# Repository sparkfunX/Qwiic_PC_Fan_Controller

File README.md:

Qwiic PC Fan Controller
========================================

[*Qwiic PC Fan Controller (SPX-18570)*](https://www.sparkfun.com/products/18570)

Whether for active cooling or ventilation, a tiny fan can make a big difference. And by that logic a big fan can make an even bigger difference! Luckily, 4-Wire PC cooling fans come in all shapes and sizes, so there's definitely one out there that's perfect for your project. The only downside is that they can be a pain to drive if you don't need them to be 100% on the throttle all the time. To remedy this, we've modified our Qwiic Blower Fan board to drive any 3- or 4-wire PC Fan with any voltage from 5 to 20VDC!

The Qwiic PC Fan Controller allows you easily control almost any PC fan over the Qwiic bus using the on board ATtiny microcontroller and control firmware. The control firmware monitors the tachometer output of the fan in order to implement PI Control over the fan speed, allowing you to set your desired speed in real units. It's also possible to disable the PI control loop and set the speed as a proportion of the maximum. The accompanying Arduino library includes example code for controlling the fan, tweaking settings, and even setting the fan speed based on an attached Qwiic Temperature Sensor and a lookup table. The on board trimpots allow you to very quickly tune the PI loop parameters to your application, but they can also be overridden by the Qwiic bus for remote configuration.

Heads Up! Without any external power supply connected, the Qwiic PC Fan Controller will attempt to drive the connected fan from the Qwiic bus. Even a very small 5V fan operates at the upper limit of the Qwiic bus' power delivery capability. If there are few other devices on the bus and the fan is not allowed to rapidly change throttle, it is possible to power a small fan directly from the bus. In most applications, however, it will be necessary to provide the PC Fan Controller with a dedicated fan power supply.

Repository Contents
-------------------

* **/Firmware** - Control firmware for the ATtiny
* **/Hardware** - Eagle design files (.brd, .sch)
* **/Production** - Panelized hardware files for production

License Information
-------------------

This product is _**open source**_! 

Please review the LICENSE.md file for license information. 

If you have any questions or concerns on licensing, please contact technical support on our [SparkFun forums](https://forum.sparkfun.com/viewforum.php?f=152).

Distributed as-is; no warranty is given.

- Your friends at SparkFun.

_<COLLABORATION CREDIT>_

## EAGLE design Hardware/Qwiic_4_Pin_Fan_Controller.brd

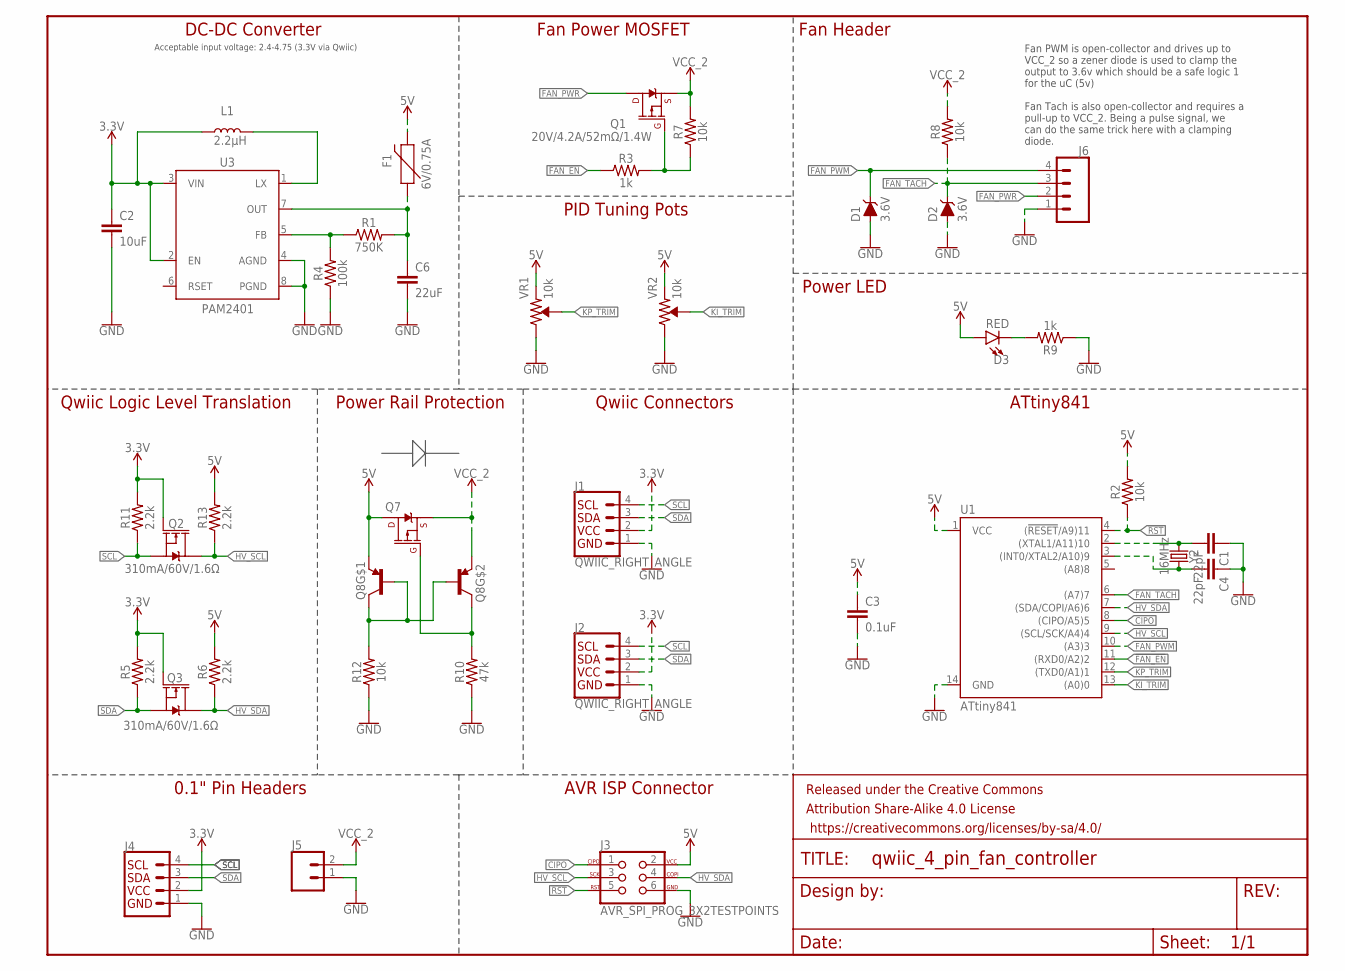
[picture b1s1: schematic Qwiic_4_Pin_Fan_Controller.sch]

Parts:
C1, C4: 22pF; 0603
C2: 10uF; 0603
C3: 0.1uF; 0603
C6: 22uF; 0805
D1, D2: 3.6V; SOD-323
D3: RED; LED-0603
F1: 6V/0.75A; 1206
FRAME1: FRAME-LETTER; CREATIVE_COMMONS
J1, J2: QWIIC_RIGHT_ANGLE; JST04_1MM_RA
J3: AVR_SPI_PROG_3X2TESTPOINTS; 2X3_TEST_POINTS
J4: I2C_STANDARD_NO_SILK; 1X04_NO_SILK
J5: CONN_021X02_NO_SILK; 1X02_NO_SILK
J6: CONN_041X04_NO_SILK; 1X04_NO_SILK
L1: 2.2μH; 0806
Q1, Q7: 20V/4.2A/52mΩ/1.4W; SOT23-3
Q2, Q3: 310mA/60V/1.6Ω; SOT323
Q8: TRANS_PNP_DUALSOT-363; SOT363_PHILIPS
R1: 750K; 0603
R2, R7, R8, R12: 10k; 0603@1
R3, R9: 1k; 0603
R4: 100k; 0603
R5, R6, R11, R13: 2.2k; 0603
R10: 47k; 0603@1
U1: ATtiny841; SO14
U3: PAM2401; MSOP8
VR1, VR2: 10k; TRIMPOT-SMD-3MM-CLOSED
Y2: 16MHz; CRYSTAL-SMD-2.0X1.6MM

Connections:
3.3V: C2.1, J1.2, J2.2, J4.2, L1.1, Q2.1 (G), Q3.1 (G), R5.2, R11.2, U3.2 (EN), U3.3 (VIN)
5V: C3.1, D3.A, F1.2, J3.2, Q7.3 (D), Q8.1 (E), R2.2, R6.2, R13.2, U1.1 (VCC), VR1.1 (CCW), VR2.1 (CCW)
!FAN_EN: R3.1, U1.11 ((RXD0/A2)2)
!RST: J3.5, R2.1, U1.4 ((!RESET!/A9)11)
CIPO: J3.1, U1.8 ((CIPO/A5)5)
FAN_PWM: D1.C, J6.4, U1.10 ((A3)3)
FAN_PWR: J6.2, Q1.3 (D)
FAN_TACH: D2.C, J6.3, R8.1, U1.6 ((A7)7)
GND: C1.1, C2.2, C3.2, C4.1, C6.2, D1.A, D2.A, J1.1, J2.1, J3.6, J4.1, J5.1, J6.1, R4.1, R9.1, R10.1, R12.1, U1.14 (GND), U3.4 (AGND), U3.8 (PGND), VR1.3 (CW), VR2.3 (CW)
HV_SCL: J3.3, Q2.3 (D), R13.1, U1.9 ((SCL/SCK/A4)4)
HV_SDA: J3.4, Q3.3 (D), R6.1, U1.7 ((SDA/COPI/A6)6)
KI_TRIM: U1.13 ((A0)0), VR2.2 (WIPER)
KP_TRIM: U1.12 ((TXD0/A1)1), VR1.2 (WIPER)
unnamed: C4.2, U1.3 ((INT0/XTAL2/A10)9), Y2.1
unnamed: R1.1, R4.2, U3.5 (FB)
unnamed: L1.2, U3.1 (LX)
unnamed: C1.2, U1.2 ((XTAL1/A11)10), Y2.3 (2)
unnamed: Q1.1 (G), R3.2, R7.1
unnamed: C6.1, F1.1, R1.2, U3.7 (OUT)
unnamed: D3.C, R9.2
unnamed: Q7.1 (G), Q8.3 (C), R10.2
unnamed: Q8.2 (B), Q8.5 (B), Q8.6 (C), R12.2
SCL: J1.4, J2.4, J4.4, Q2.2 (S), R11.1
SDA: J1.3, J2.3, J4.3, Q3.2 (S), R5.1
VCC_2: J5.2, Q1.2 (S), Q7.2 (S), Q8.4 (E), R7.2, R8.2

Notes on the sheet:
DC-DC Converter
Acceptable input voltage: 2.4-4.75 (3.3V via Qwiic)
ATtiny841
Qwiic Connectors
Qwiic Logic Level Translation
0.1" Pin Headers
AVR ISP Connector
Fan Power MOSFET
Fan Header
Fan PWM is open-collector and drives up to VCC_2 so a zener diode is used to clamp the output to 3.6v which should be a safe logic 1 for the uC (5v) Fan Tach is also open-collector and requires a pull-up to VCC_2. Being a pulse signal, we can do the same trick here with a clamping diode.
PID Tuning Pots
Power LED
Power Rail Protection

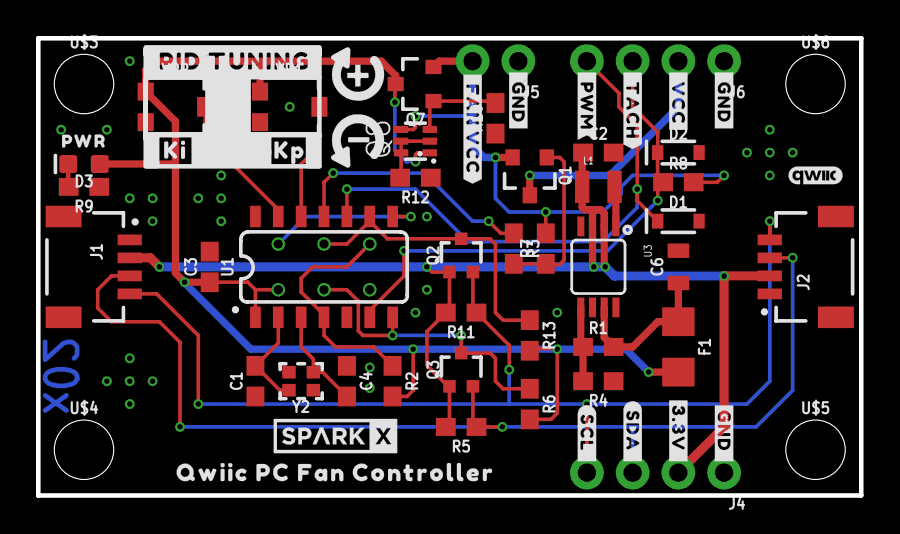
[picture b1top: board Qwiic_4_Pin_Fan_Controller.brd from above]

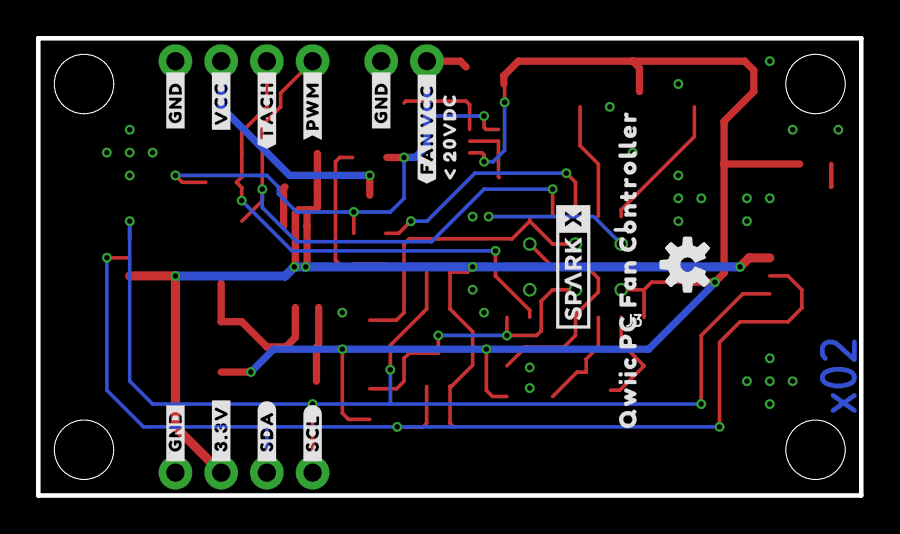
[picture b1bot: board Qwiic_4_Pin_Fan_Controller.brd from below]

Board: 2 copper layers, 45.7 x 25.4 mm, 76 parts (15 on the bottom side), 25 nets.

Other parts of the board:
U$1, U$9, U$21: #_GND#0
U$2: #_VCC#0
U$3, U$4, U$5, U$6: STAND-OFF
U$7: #_TACH#0
U$8: #_PWM#0
U$10, U$20, U$26: #GND_#0
U$11: #3#3V_#0
U$12: #SDA_#0
U$13: #SCL_#0
U$14: #PID_TUNING0
U$15: KI0
U$16: KP0
U$17: QWIIC_3MM
U$18, U$36: SPARKX-SMALL
U$19: #_FAN_VCC#0
U$22: PWR0
U$23: #VCC_#0
U$24: #TACH_#0
U$25: #PWM_#0
U$27: #_3#3V#0
U$28: #_SDA#0
U$29: #_SCL#0
U$30, U$35: QWIIC_PC_FAN_CONTROLLER0
U$31: #FAN_VCC_#0
U$32: _#_20VDC0
U$37: OSHW-LOGO-S
U$38: TURN_INDICATOR#SVG0

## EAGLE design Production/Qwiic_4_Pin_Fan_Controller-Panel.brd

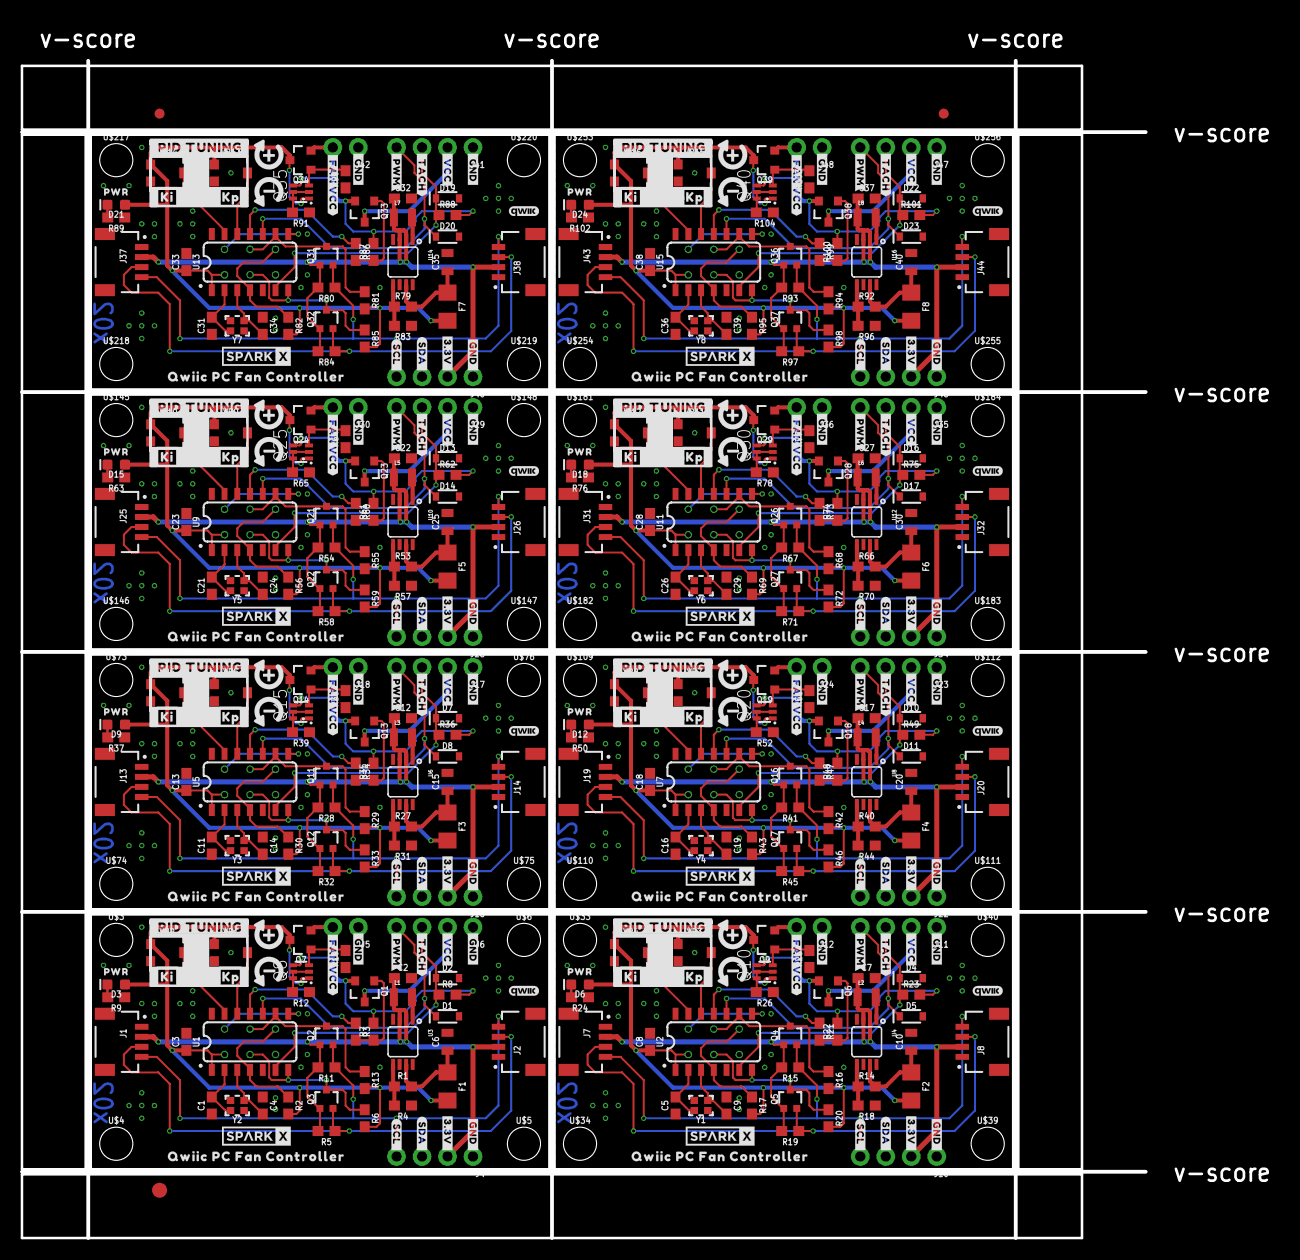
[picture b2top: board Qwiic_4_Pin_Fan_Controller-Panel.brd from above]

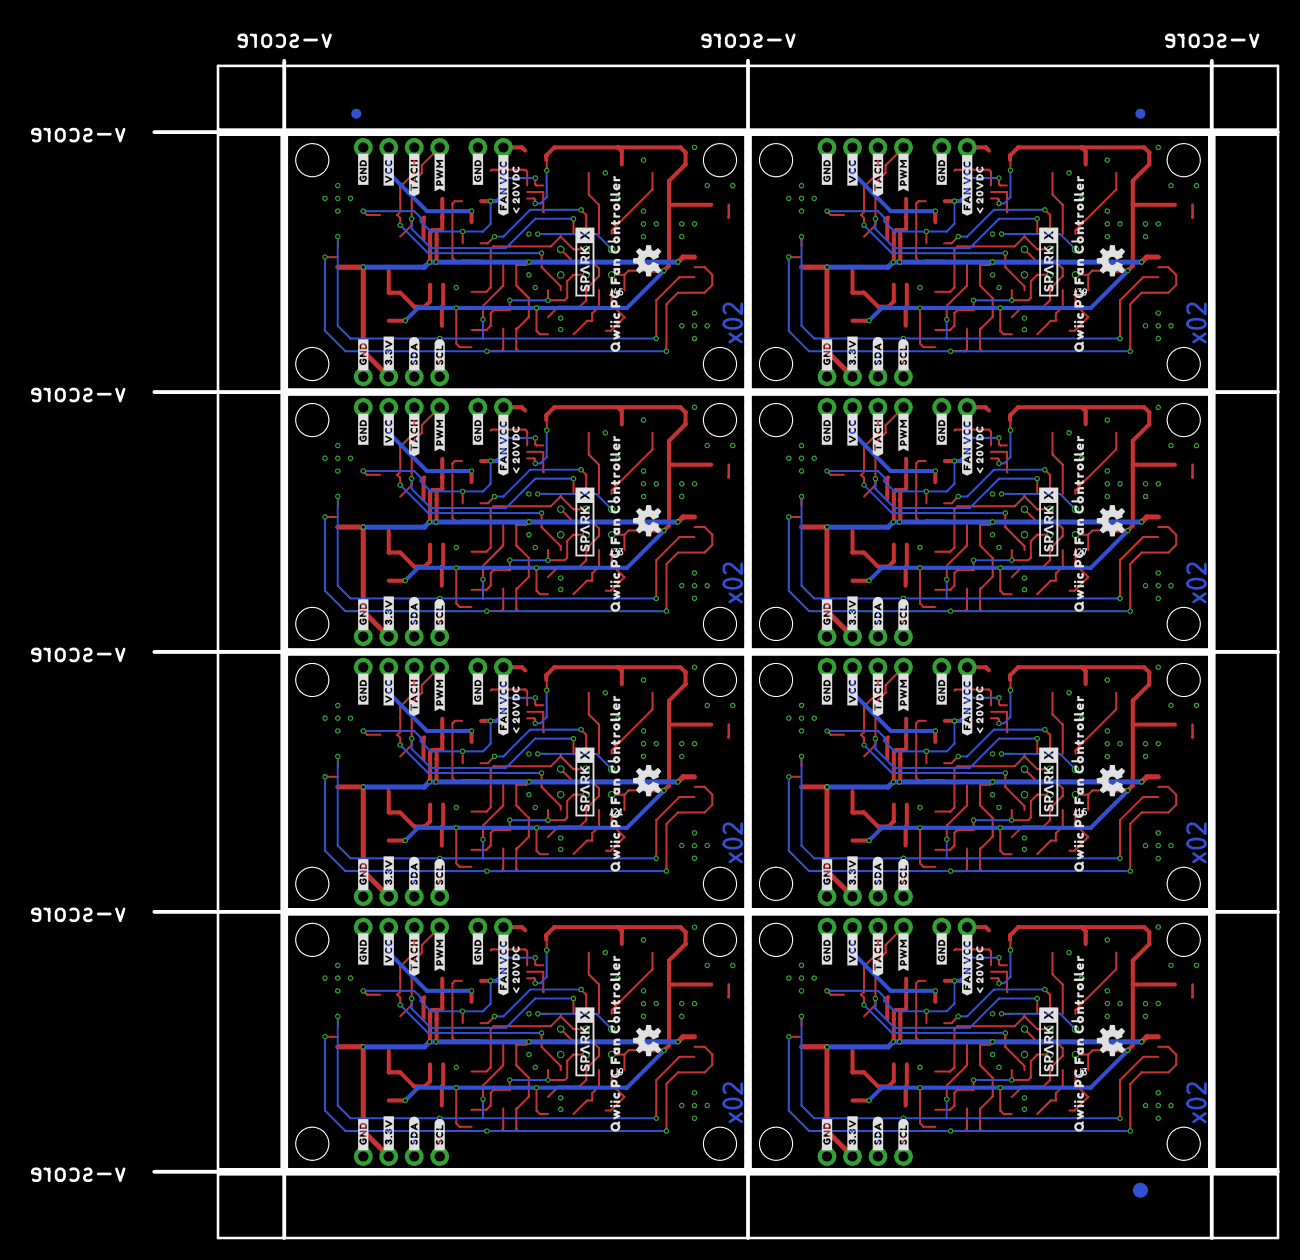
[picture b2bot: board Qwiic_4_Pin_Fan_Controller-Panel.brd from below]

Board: 2 copper layers, 125.2 x 121.2 mm, 606 parts (123 on the bottom side), 200 nets.

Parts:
C1, C4, C5, C9, C11, C14, C16, C19, C21, C24, C26, C29, C31, C34, C36, C39: 22pF; 0603
C2, C7, C12, C17, C22, C27, C32, C37: 10uF; 0603
C3, C8, C13, C18, C23, C28, C33, C38: 0.1uF; 0603
C6, C10, C15, C20, C25, C30, C35, C40: 22uF; 0805
D1, D2, D4, D5, D7, D8, D10, D11, D13, D14, D16, D17, D19, D20, D22, D23: 3.6V; SOD-323
D3, D6, D9, D12, D15, D18, D21, D24: RED; LED-0603
E$1, E$2, E$3, E$4: FIDUCIAL-1X2
E$5, E$6: FIDUCIAL-1.5X3
F1, F2, F3, F4, F5, F6, F7, F8: 6V/0.75A; 1206
J1, J2, J7, J8, J13, J14, J19, J20, J25, J26, J31, J32, J37, J38, J43, J44: QWIIC_RIGHT_ANGLE; JST04_1MM_RA
J3, J9, J15, J21, J27, J33, J39, J45: AVR_SPI_PROG_3X2TESTPOINTS; 2X3_TEST_POINTS
J4, J6, J10, J11, J16, J17, J22, J23, J28, J29, J34, J35, J40, J41, J46, J47: 1X04_NO_SILK
J5, J12, J18, J24, J30, J36, J42, J48: 1X02_NO_SILK
L1, L2, L3, L4, L5, L6, L7, L8: 2.2μH; 0806
Q1, Q6, Q7, Q9, Q13, Q14, Q18, Q19, Q23, Q24, Q28, Q29, Q33, Q34, Q38, Q39: 20V/4.2A/52mΩ/1.4W; SOT23-3
Q2, Q3, Q4, Q5, Q11, Q12, Q16, Q17, Q21, Q22, Q26, Q27, Q31, Q32, Q36, Q37: 310mA/60V/1.6Ω; SOT323
Q8, Q10, Q15, Q20, Q25, Q30, Q35, Q40: SOT363_PHILIPS
R1, R14, R27, R40, R53, R66, R79, R92: 750K; 0603
R2, R7, R8, R12, R17, R22, R23, R26, R30, R35, R36, R39, R43, R48, R49, R52, R56, R61, R62, R65, R69, R74, R75, R78, R82, R87, R88, R91, R95, R100, R101, R104: 10k; 0603@1
R3, R9, R21, R24, R34, R37, R47, R50, R60, R63, R73, R76, R86, R89, R99, R102: 1k; 0603
R4, R18, R31, R44, R57, R70, R83, R96: 100k; 0603
R5, R6, R11, R13, R15, R16, R19, R20, R28, R29, R32, R33, R41, R42, R45, R46, R54, R55, R58, R59, R67, R68, R71, R72, R80, R81, R84, R85, R93, R94, R97, R98: 2.2k; 0603
R10, R25, R38, R51, R64, R77, R90, R103: 47k; 0603@1
U1, U2, U5, U7, U9, U11, U13, U15: ATtiny841; SO14
U3, U4, U6, U8, U10, U12, U14, U16: PAM2401; MSOP8
U$1, U$9, U$21, U$41, U$45, U$53, U$77, U$81, U$89, U$113, U$117, U$125, U$149, U$153, U$161, U$185, U$189, U$197, U$221, U$225, U$233, U$257, U$261, U$269: #_GND#0
U$2, U$42, U$78, U$114, U$150, U$186, U$222, U$258: #_VCC#0
U$3, U$4, U$5, U$6, U$33, U$34, U$39, U$40, U$73, U$74, U$75, U$76, U$109, U$110, U$111, U$112, U$145, U$146, U$147, U$148, U$181, U$182, U$183, U$184, U$217, U$218, U$219, U$220, U$253, U$254, U$255, U$256: STAND-OFF
U$7, U$43, U$79, U$115, U$151, U$187, U$223, U$259: #_TACH#0
U$8, U$44, U$80, U$116, U$152, U$188, U$224, U$260: #_PWM#0
U$10, U$20, U$26, U$46, U$52, U$57, U$82, U$88, U$93, U$118, U$124, U$129, U$154, U$160, U$165, U$190, U$196, U$201, U$226, U$232, U$237, U$262, U$268, U$273: #GND_#0
U$11, U$47, U$83, U$119, U$155, U$191, U$227, U$263: #3#3V_#0
U$12, U$48, U$84, U$120, U$156, U$192, U$228, U$264: #SDA_#0
U$13, U$49, U$85, U$121, U$157, U$193, U$229, U$265: #SCL_#0
U$14, U$66, U$102, U$138, U$174, U$210, U$246, U$282: #PID_TUNING0
U$15, U$67, U$103, U$139, U$175, U$211, U$247, U$283: KI0
U$16, U$68, U$104, U$140, U$176, U$212, U$248, U$284: KP0
U$17, U$50, U$86, U$122, U$158, U$194, U$230, U$266: QWIIC_3MM
U$18, U$36, U$51, U$62, U$87, U$98, U$123, U$134, U$159, U$170, U$195, U$206, U$231, U$242, U$267, U$278: SPARKX-SMALL
U$19, U$65, U$101, U$137, U$173, U$209, U$245, U$281: #_FAN_VCC#0
U$22, U$69, U$105, U$141, U$177, U$213, U$249, U$285: PWR0
U$23, U$54, U$90, U$126, U$162, U$198, U$234, U$270: #VCC_#0
U$24, U$55, U$91, U$127, U$163, U$199, U$235, U$271: #TACH_#0
U$25, U$56, U$92, U$128, U$164, U$200, U$236, U$272: #PWM_#0
U$27, U$58, U$94, U$130, U$166, U$202, U$238, U$274: #_3#3V#0
U$28, U$59, U$95, U$131, U$167, U$203, U$239, U$275: #_SDA#0
U$29, U$60, U$96, U$132, U$168, U$204, U$240, U$276: #_SCL#0
U$30, U$35, U$61, U$63, U$97, U$99, U$133, U$135, U$169, U$171, U$205, U$207, U$241, U$243, U$277, U$279: QWIIC_PC_FAN_CONTROLLER0
U$31, U$71, U$107, U$143, U$179, U$215, U$251, U$287: #FAN_VCC_#0
U$32, U$72, U$108, U$144, U$180, U$216, U$252, U$288: _#_20VDC0
U$37, U$64, U$100, U$136, U$172, U$208, U$244, U$280: OSHW-LOGO-S
U$38, U$70, U$106, U$142, U$178, U$214, U$250, U$286: TURN_INDICATOR#SVG0
VR1, VR2, VR3, VR4, VR5, VR6, VR7, VR8, VR9, VR10, VR11, VR12, VR13, VR14, VR15, VR16: 10k; TRIMPOT-SMD-3MM-CLOSED
Y1, Y2, Y3, Y4, Y5, Y6, Y7, Y8: 16MHz; CRYSTAL-SMD-2.0X1.6MM

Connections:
3.3V: C2.1, J1.2, J2.2, J4.2, L1.1, Q2.1, Q3.1, R5.2, R11.2, U3.2, U3.3
3.3V1: C7.1, J7.2, J8.2, J10.2, L2.1, Q4.1, Q5.1, R15.2, R19.2, U4.2, U4.3
3.3V2: C12.1, J13.2, J14.2, J16.2, L3.1, Q11.1, Q12.1, R28.2, R32.2, U6.2, U6.3
3.3V3: C17.1, J19.2, J20.2, J22.2, L4.1, Q16.1, Q17.1, R41.2, R45.2, U8.2, U8.3
3.3V4: C22.1, J25.2, J26.2, J28.2, L5.1, Q21.1, Q22.1, R54.2, R58.2, U10.2, U10.3
3.3V5: C27.1, J31.2, J32.2, J34.2, L6.1, Q26.1, Q27.1, R67.2, R71.2, U12.2, U12.3
3.3V6: C32.1, J37.2, J38.2, J40.2, L7.1, Q31.1, Q32.1, R80.2, R84.2, U14.2, U14.3
3.3V7: C37.1, J43.2, J44.2, J46.2, L8.1, Q36.1, Q37.1, R93.2, R97.2, U16.2, U16.3
5V: C3.1, D3.A, F1.2, J3.2, Q7.3, Q8.1, R2.2, R6.2, R13.2, U1.1, VR1.1, VR2.1
5V1: C8.1, D6.A, F2.2, J9.2, Q9.3, Q10.1, R16.2, R17.2, R20.2, U2.1, VR3.1, VR4.1
5V2: C13.1, D9.A, F3.2, J15.2, Q14.3, Q15.1, R29.2, R30.2, R33.2, U5.1, VR5.1, VR6.1
5V3: C18.1, D12.A, F4.2, J21.2, Q19.3, Q20.1, R42.2, R43.2, R46.2, U7.1, VR7.1, VR8.1
5V4: C23.1, D15.A, F5.2, J27.2, Q24.3, Q25.1, R55.2, R56.2, R59.2, U9.1, VR9.1, VR10.1
5V5: C28.1, D18.A, F6.2, J33.2, Q29.3, Q30.1, R68.2, R69.2, R72.2, U11.1, VR11.1, VR12.1
5V6: C33.1, D21.A, F7.2, J39.2, Q34.3, Q35.1, R81.2, R82.2, R85.2, U13.1, VR13.1, VR14.1
5V7: C38.1, D24.A, F8.2, J45.2, Q39.3, Q40.1, R94.2, R95.2, R98.2, U15.1, VR15.1, VR16.1
!FAN_EN: R3.1, U1.11
!FAN_EN1: R21.1, U2.11
!FAN_EN2: R34.1, U5.11
!FAN_EN3: R47.1, U7.11
!FAN_EN4: R60.1, U9.11
!FAN_EN5: R73.1, U11.11
!FAN_EN6: R86.1, U13.11
!FAN_EN7: R99.1, U15.11
!RST: J3.5, R2.1, U1.4
!RST1: J9.5, R17.1, U2.4
!RST2: J15.5, R30.1, U5.4
!RST3: J21.5, R43.1, U7.4
!RST4: J27.5, R56.1, U9.4
!RST5: J33.5, R69.1, U11.4
!RST6: J39.5, R82.1, U13.4
!RST7: J45.5, R95.1, U15.4
CIPO: J3.1, U1.8
CIPO1: J9.1, U2.8
CIPO2: J15.1, U5.8
CIPO3: J21.1, U7.8
CIPO4: J27.1, U9.8
CIPO5: J33.1, U11.8
CIPO6: J39.1, U13.8
CIPO7: J45.1, U15.8
FAN_PWM: D1.C, J6.4, U1.10
FAN_PWM1: D5.C, J11.4, U2.10
FAN_PWM2: D8.C, J17.4, U5.10
FAN_PWM3: D11.C, J23.4, U7.10
FAN_PWM4: D14.C, J29.4, U9.10
FAN_PWM5: D17.C, J35.4, U11.10
FAN_PWM6: D20.C, J41.4, U13.10
FAN_PWM7: D23.C, J47.4, U15.10
FAN_PWR: J6.2, Q1.3
FAN_PWR1: J11.2, Q6.3
FAN_PWR2: J17.2, Q13.3
FAN_PWR3: J23.2, Q18.3
FAN_PWR4: J29.2, Q23.3
FAN_PWR5: J35.2, Q28.3
FAN_PWR6: J41.2, Q33.3
FAN_PWR7: J47.2, Q38.3
FAN_TACH: D2.C, J6.3, R8.1, U1.6
FAN_TACH1: D4.C, J11.3, R23.1, U2.6
FAN_TACH2: D7.C, J17.3, R36.1, U5.6
FAN_TACH3: D10.C, J23.3, R49.1, U7.6
FAN_TACH4: D13.C, J29.3, R62.1, U9.6
FAN_TACH5: D16.C, J35.3, R75.1, U11.6
FAN_TACH6: D19.C, J41.3, R88.1, U13.6
FAN_TACH7: D22.C, J47.3, R101.1, U15.6
GND: C1.1, C2.2, C3.2, C4.1, C6.2, D1.A, D2.A, J1.1, J2.1, J3.6, J4.1, J5.1, J6.1, R4.1, R9.1, R10.1, R12.1, U1.14, U3.4, U3.8, VR1.3, VR2.3
GND1: C5.1, C7.2, C8.2, C9.1, C10.2, D4.A, D5.A, J7.1, J8.1, J9.6, J10.1, J11.1, J12.1, R18.1, R24.1, R25.1, R26.1, U2.14, U4.4, U4.8, VR3.3, VR4.3
GND2: C11.1, C12.2, C13.2, C14.1, C15.2, D7.A, D8.A, J13.1, J14.1, J15.6, J16.1, J17.1, J18.1, R31.1, R37.1, R38.1, R39.1, U5.14, U6.4, U6.8, VR5.3, VR6.3
GND3: C16.1, C17.2, C18.2, C19.1, C20.2, D10.A, D11.A, J19.1, J20.1, J21.6, J22.1, J23.1, J24.1, R44.1, R50.1, R51.1, R52.1, U7.14, U8.4, U8.8, VR7.3, VR8.3
GND4: C21.1, C22.2, C23.2, C24.1, C25.2, D13.A, D14.A, J25.1, J26.1, J27.6, J28.1, J29.1, J30.1, R57.1, R63.1, R64.1, R65.1, U9.14, U10.4, U10.8, VR9.3, VR10.3
GND5: C26.1, C27.2, C28.2, C29.1, C30.2, D16.A, D17.A, J31.1, J32.1, J33.6, J34.1, J35.1, J36.1, R70.1, R76.1, R77.1, R78.1, U11.14, U12.4, U12.8, VR11.3, VR12.3
GND6: C31.1, C32.2, C33.2, C34.1, C35.2, D19.A, D20.A, J37.1, J38.1, J39.6, J40.1, J41.1, J42.1, R83.1, R89.1, R90.1, R91.1, U13.14, U14.4, U14.8, VR13.3, VR14.3
GND7: C36.1, C37.2, C38.2, C39.1, C40.2, D22.A, D23.A, J43.1, J44.1, J45.6, J46.1, J47.1, J48.1, R96.1, R102.1, R103.1, R104.1, U15.14, U16.4, U16.8, VR15.3, VR16.3
HV_SCL: J3.3, Q2.3, R13.1, U1.9
HV_SCL1: J9.3, Q4.3, R16.1, U2.9
HV_SCL2: J15.3, Q11.3, R29.1, U5.9
HV_SCL3: J21.3, Q16.3, R42.1, U7.9
HV_SCL4: J27.3, Q21.3, R55.1, U9.9
HV_SCL5: J33.3, Q26.3, R68.1, U11.9
HV_SCL6: J39.3, Q31.3, R81.1, U13.9
HV_SCL7: J45.3, Q36.3, R94.1, U15.9
HV_SDA: J3.4, Q3.3, R6.1, U1.7
HV_SDA1: J9.4, Q5.3, R20.1, U2.7
HV_SDA2: J15.4, Q12.3, R33.1, U5.7
HV_SDA3: J21.4, Q17.3, R46.1, U7.7
HV_SDA4: J27.4, Q22.3, R59.1, U9.7
HV_SDA5: J33.4, Q27.3, R72.1, U11.7
HV_SDA6: J39.4, Q32.3, R85.1, U13.7
HV_SDA7: J45.4, Q37.3, R98.1, U15.7
KI_TRIM: U1.13, VR2.2
KI_TRIM1: U2.13, VR4.2
KI_TRIM2: U5.13, VR6.2
KI_TRIM3: U7.13, VR8.2
KI_TRIM4: U9.13, VR10.2
KI_TRIM5: U11.13, VR12.2
KI_TRIM6: U13.13, VR14.2
KI_TRIM7: U15.13, VR16.2
KP_TRIM: U1.12, VR1.2
KP_TRIM1: U2.12, VR3.2
KP_TRIM2: U5.12, VR5.2
KP_TRIM3: U7.12, VR7.2
KP_TRIM4: U9.12, VR9.2
KP_TRIM5: U11.12, VR11.2
KP_TRIM6: U13.12, VR13.2
KP_TRIM7: U15.12, VR15.2
unnamed: C4.2, U1.3, Y2.1
unnamed: R1.1, R4.2, U3.5
unnamed: L1.2, U3.1
unnamed: C1.2, U1.2, Y2.3
unnamed: Q1.1, R3.2, R7.1
unnamed: C6.1, F1.1, R1.2, U3.7
unnamed: D3.C, R9.2
unnamed: R14.1, R18.2, U4.5
unnamed: L2.2, U4.1
unnamed: C9.2, U2.3, Y1.1
unnamed: C5.2, U2.2, Y1.3
unnamed: Q6.1, R21.2, R22.1
unnamed: C10.1, F2.1, R14.2, U4.7
unnamed: D6.C, R24.2
unnamed: Q7.1, Q8.3, R10.2
unnamed: Q8.2, Q8.5, Q8.6, R12.2
unnamed: Q9.1, Q10.3, R25.2
unnamed: Q10.2, Q10.5, Q10.6, R26.2
unnamed: R27.1, R31.2, U6.5
unnamed: L3.2, U6.1
unnamed: C14.2, U5.3, Y3.1
unnamed: C11.2, U5.2, Y3.3
unnamed: Q13.1, R34.2, R35.1
unnamed: C15.1, F3.1, R27.2, U6.7
unnamed: D9.C, R37.2
unnamed: Q14.1, Q15.3, R38.2
unnamed: Q15.2, Q15.5, Q15.6, R39.2
unnamed: R40.1, R44.2, U8.5
unnamed: L4.2, U8.1
unnamed: C19.2, U7.3, Y4.1
unnamed: C16.2, U7.2, Y4.3
unnamed: Q18.1, R47.2, R48.1
unnamed: C20.1, F4.1, R40.2, U8.7
unnamed: D12.C, R50.2
unnamed: Q19.1, Q20.3, R51.2
unnamed: Q20.2, Q20.5, Q20.6, R52.2
unnamed: R53.1, R57.2, U10.5
unnamed: L5.2, U10.1
unnamed: C24.2, U9.3, Y5.1
unnamed: C21.2, U9.2, Y5.3
unnamed: Q23.1, R60.2, R61.1
unnamed: C25.1, F5.1, R53.2, U10.7
unnamed: D15.C, R63.2
unnamed: Q24.1, Q25.3, R64.2
unnamed: Q25.2, Q25.5, Q25.6, R65.2
unnamed: R66.1, R70.2, U12.5
unnamed: L6.2, U12.1
unnamed: C29.2, U11.3, Y6.1
unnamed: C26.2, U11.2, Y6.3
unnamed: Q28.1, R73.2, R74.1
unnamed: C30.1, F6.1, R66.2, U12.7
unnamed: D18.C, R76.2
unnamed: Q29.1, Q30.3, R77.2
unnamed: Q30.2, Q30.5, Q30.6, R78.2
unnamed: R79.1, R83.2, U14.5
unnamed: L7.2, U14.1
unnamed: C34.2, U13.3, Y7.1
unnamed: C31.2, U13.2, Y7.3
unnamed: Q33.1, R86.2, R87.1
unnamed: C35.1, F7.1, R79.2, U14.7
unnamed: D21.C, R89.2
unnamed: Q34.1, Q35.3, R90.2
unnamed: Q35.2, Q35.5, Q35.6, R91.2
unnamed: R92.1, R96.2, U16.5
unnamed: L8.2, U16.1
unnamed: C39.2, U15.3, Y8.1
unnamed: C36.2, U15.2, Y8.3
unnamed: Q38.1, R99.2, R100.1
unnamed: C40.1, F8.1, R92.2, U16.7
unnamed: D24.C, R102.2
unnamed: Q39.1, Q40.3, R103.2
unnamed: Q40.2, Q40.5, Q40.6, R104.2
SCL: J1.4, J2.4, J4.4, Q2.2, R11.1
SCL1: J7.4, J8.4, J10.4, Q4.2, R15.1
SCL2: J13.4, J14.4, J16.4, Q11.2, R28.1
SCL3: J19.4, J20.4, J22.4, Q16.2, R41.1
SCL4: J25.4, J26.4, J28.4, Q21.2, R54.1
SCL5: J31.4, J32.4, J34.4, Q26.2, R67.1
SCL6: J37.4, J38.4, J40.4, Q31.2, R80.1
SCL7: J43.4, J44.4, J46.4, Q36.2, R93.1
SDA: J1.3, J2.3, J4.3, Q3.2, R5.1
SDA1: J7.3, J8.3, J10.3, Q5.2, R19.1
SDA2: J13.3, J14.3, J16.3, Q12.2, R32.1
SDA3: J19.3, J20.3, J22.3, Q17.2, R45.1
SDA4: J25.3, J26.3, J28.3, Q22.2, R58.1
SDA5: J31.3, J32.3, J34.3, Q27.2, R71.1
SDA6: J37.3, J38.3, J40.3, Q32.2, R84.1
SDA7: J43.3, J44.3, J46.3, Q37.2, R97.1
VCC_1: J12.2, Q6.2, Q9.2, Q10.4, R22.2, R23.2
VCC_2: J5.2, Q1.2, Q7.2, Q8.4, R7.2, R8.2
VCC_3: J18.2, Q13.2, Q14.2, Q15.4, R35.2, R36.2
VCC_4: J24.2, Q18.2, Q19.2, Q20.4, R48.2, R49.2
VCC_5: J30.2, Q23.2, Q24.2, Q25.4, R61.2, R62.2
VCC_6: J36.2, Q28.2, Q29.2, Q30.4, R74.2, R75.2
VCC_7: J42.2, Q33.2, Q34.2, Q35.4, R87.2, R88.2
VCC_8: J48.2, Q38.2, Q39.2, Q40.4, R100.2, R101.2

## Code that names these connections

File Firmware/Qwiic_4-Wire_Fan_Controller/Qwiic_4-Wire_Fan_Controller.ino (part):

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/* PIN ASSIGNMENTS */
#define PIN_TRIM_KI 0    // ADC in from trimpot
#define PIN_TRIM_KP 1    // ADC in from trimpot
#define PIN_FAN_ENABLE 2 // DO to !FAN_EN
#define PIN_PWM_OUT 3    // DO to FAN_PWM
#define PIN_TACH_IN 7    // DI from FAN_TACH

/* I²C STUFF */
#define MAX_SENT_BYTES 0x05 // Used to ignore invalid commands
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
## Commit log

2021-07-19 x01 PCBs ordered
2021-10-17 Firmware too big
    Saving the combined firmware for posterity.
    It's 500bytes too big, so I'm gonna split it.
2021-10-21 Update Qwiic_4-Wire_Fan_Controller.ino
    Firmware works, doing some final PI tuning and writing the controller-side code
2021-10-25 Update Qwiic_4-Wire_Fan_Controller.ino
    Update to semifinal firmware
2021-10-27 Firmware Final Tuning
2021-10-27 Firmware Rename
    Making all naming consistent across Sparkle, Github, Arduino
2021-10-29 Minor firmware fixes
2021-11-13 x02
    I exploded the proto by applying 12VDC without cutting the jumper.
    If I can do it, a customer _will_ do it.
    I've replaced the jumper with a mosfet "diode" protection circuit.
2021-11-13 x02 silk change and gerbers
    -Fix a silk label on the bottom
    -Panelize and CAM Production Files
2022-02-10 Move hardware files into hardware dir
2022-02-10 Adding programming batch.
2022-02-10 Updated Firmware
    - Firmware update pulled from Blower Fan
    - Add Compiled Binary from new firmware
    - Add Programming batch file with correct fuse bits

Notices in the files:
parts and their libraries:
SparkFun-Capacitors: Licensing: Creative Commons ShareAlike 4.0 International - https://creativecommons.org/licenses/by-sa/4.0
SparkFun-Aesthetics: Released under the Creative Commons Attribution Share-Alike 4.0 License
SparkFun-Aesthetics: https://creativecommons.org/licenses/by-sa/4.0
